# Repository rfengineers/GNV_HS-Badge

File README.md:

# GNV_HS-Badge
Gainesville Hackerspace name-badge project 1

Our first pass at a single-sided aluminum printed circuit board.  The PCB is laid out in KiCAD.  

The microcontroller is a AVR 0-Series ATTINY202.  

The initial firmware is written in the Arduino IDE.  See https://github.com/SpenceKonde/megaTinyCore/ for the board manager.

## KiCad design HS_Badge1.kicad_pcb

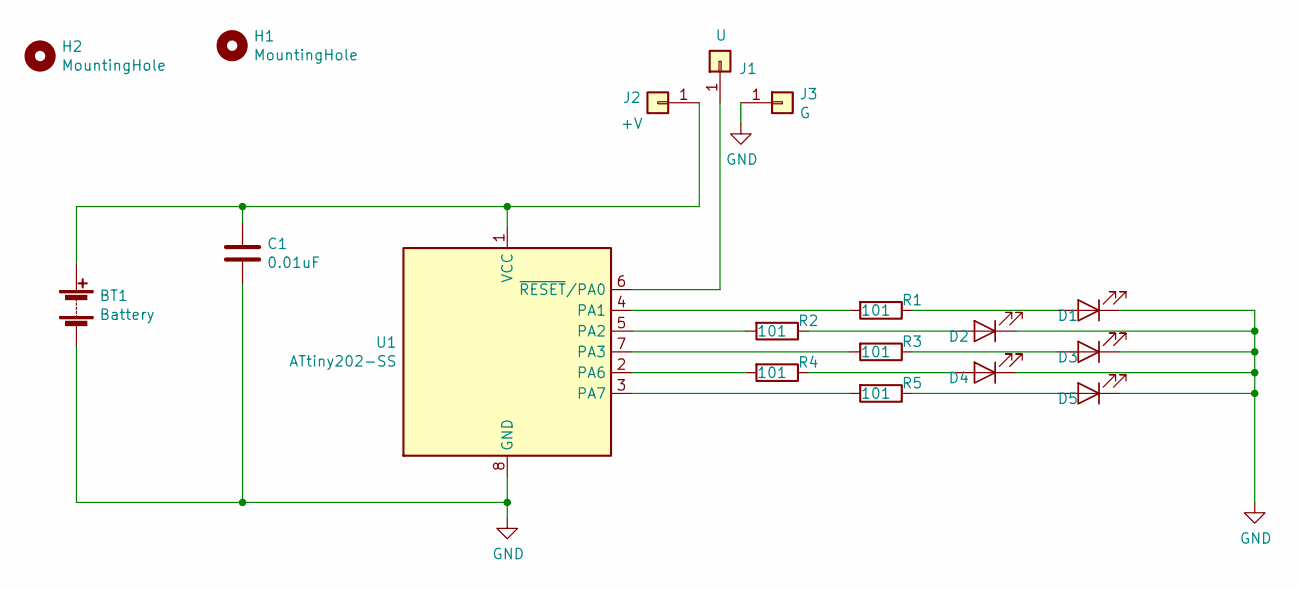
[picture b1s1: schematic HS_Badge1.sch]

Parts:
BT1: Battery; BatteryHolder_Keystone_1058_1x2032
C1: 0.01uF; C_0603_1608Metric_Pad1.05x0.95mm_HandSolder
D1, D2, D3, D4, D5: LED; LED_0603_1608Metric_Pad1.05x0.95mm_HandSolder
H1, H2: MountingHole; MountingHole_2.5mm
J1: U; TestPoint_Pad_D1.5mm
J2: +V; TestPoint_Pad_D1.5mm
J3: G; TestPoint_Pad_D1.5mm
R1, R2, R3, R4, R5: 101; R_0603_1608Metric_Pad1.05x0.95mm_HandSolder
U1: ATtiny202-SS; SOIC-8_3.9x4.9mm_P1.27mm

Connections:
GND: BT1.2 (-), C1.2, D1.1 (K), D2.1 (K), D3.1 (K), D4.1 (K), D5.1 (K), J3.1, U1.8 (GND)
unnamed: BT1.1 (+), C1.1, J2.1, U1.1 (VCC)
unnamed: D1.2 (A), R1.1
unnamed: D2.2 (A), R2.1
unnamed: D3.2 (A), R3.1
unnamed: D4.2 (A), R4.1
unnamed: D5.2 (A), R5.1
unnamed: J1.1, U1.6 (~RESET~/PA0)
unnamed: R1.2, U1.4 (PA1)
unnamed: R2.2, U1.5 (PA2)
unnamed: R3.2, U1.7 (PA3)
unnamed: R4.2, U1.2 (PA6)
unnamed: R5.2, U1.3 (PA7)

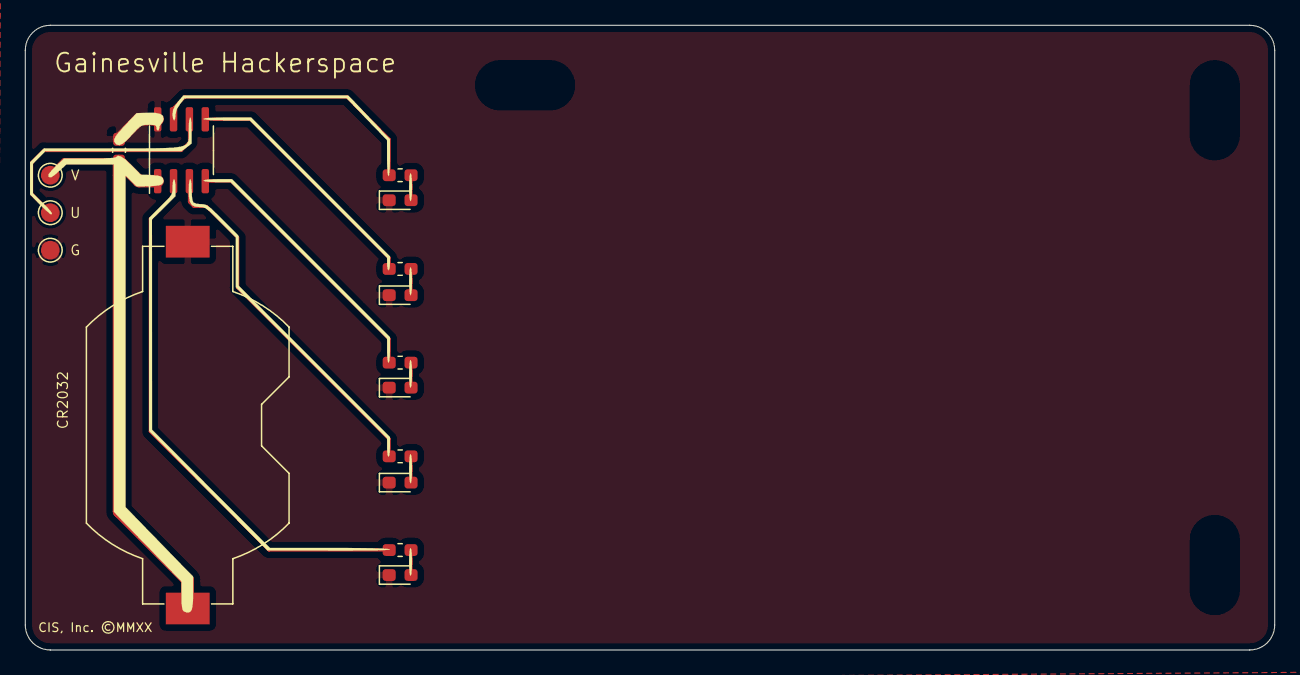
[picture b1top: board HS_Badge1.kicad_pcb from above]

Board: 2 copper layers, 100.0 x 50.0 mm, 19 parts (0 on the bottom side), 13 nets.

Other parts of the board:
H2#2: MountingHole; MountingHole_2.5mm

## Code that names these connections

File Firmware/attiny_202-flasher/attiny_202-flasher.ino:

//Compled for ATTINY202
//BoardManager: https://github.com/SpenceKonde/megaTinyCore/
#define F_CPU 1000000

void setup() {
    delay(50);
    randomSeed(ADC_TEMPERATURE);
    PORTA.DIR = 0b11001110;  // set PA1, 2, 3, 6 and 7 as outputs
    PORTA.OUTCLR = PIN1_bm;  // turn off PA1
    PORTA.OUTCLR = PIN2_bm;  // turn off PA2
    PORTA.OUTCLR = PIN3_bm;  // turn off PA3
    PORTA.OUTCLR = PIN6_bm;  // turn off PA6
    PORTA.OUTCLR = PIN7_bm;  // turn off PA7
    delay(500);
}

void loop() {
  delay(random(400,1000));//wait between 100 and 400 mSec before looping again.
  byte newVal = random(0,255);//a new random byte
  PORTA.OUT = newVal;//change the LED outputs to track the new random byte.
  
}

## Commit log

2020-07-19 added an image of the badge
2020-07-24 added stencil
2020-08-12 firmware
2020-10-24 created laser template

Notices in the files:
HS_Badge1.kicad_pcb:
CIS, Inc. ©MMXX
